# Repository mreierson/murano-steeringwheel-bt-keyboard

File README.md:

# Murano Steering Wheel Bluetooth Keyboard

Adafruit Feather board for interfacing with the Murano computer to convert steering wheel button presses into Bluetooth key strokes to control media on phone.

## Notes

SIG_YELLOW = Wire #6 - Steering Wheel Signal A  
SIG_BLUE = Wire #16 - Steering Wheel Signal B  
SIG_GND = Wire #15 - Steering Wheel Signal GND  

Buttons produce a 1-5V which is level-converted with resistor divider and connected to two analog inputs on the Feather.

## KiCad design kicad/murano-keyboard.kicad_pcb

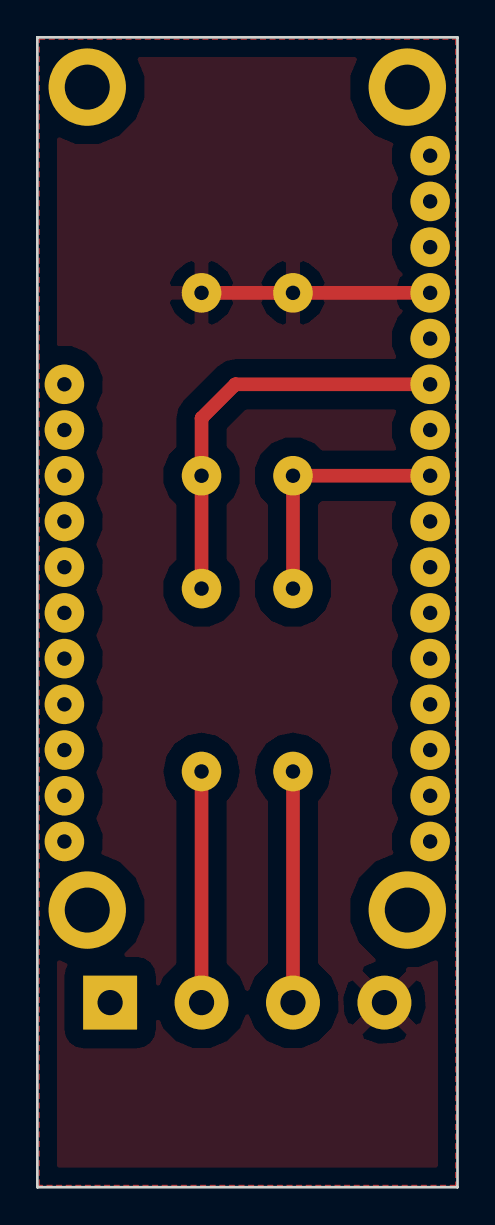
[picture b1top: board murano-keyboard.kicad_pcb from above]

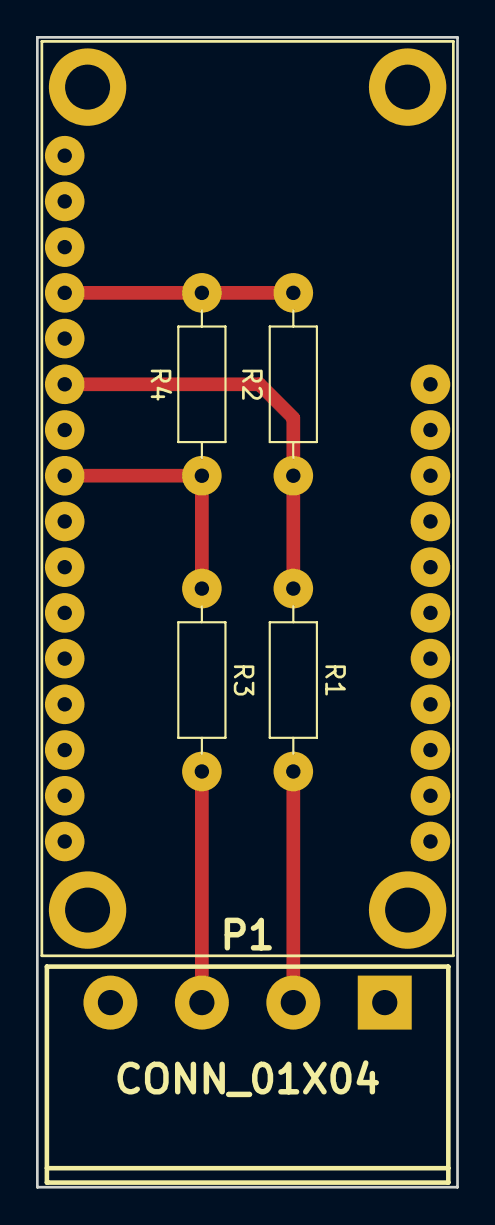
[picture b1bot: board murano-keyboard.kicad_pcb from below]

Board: 2 copper layers, 23.3 x 63.9 mm, 6 parts (6 on the bottom side), 5 nets.

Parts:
P1: CONN_01X04; mstba_2,5%2f4-g-5,08
R1, R2, R3, R4: R; R_Axial_DIN0207_L6.3mm_D2.5mm_P10.16mm_Horizontal
U1: FEATHER_32U4_BLE; FEATHER32U4BLE

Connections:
INPUT_BLUE: R3.2, R4.1, U1.8
INPUT_YELLOW: R1.2, R2.1, U1.6
SIG_BLUE: P1.3, R3.1
SIG_GND: R2.2, R4.2, U1.4
SIG_YELLOW: P1.2, R1.1

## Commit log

2018-08-24 Readme line break correction
2018-08-27 Updated to use KiCad 5
